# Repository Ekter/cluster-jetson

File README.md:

# cluster-jetson
cluster of jetson nano

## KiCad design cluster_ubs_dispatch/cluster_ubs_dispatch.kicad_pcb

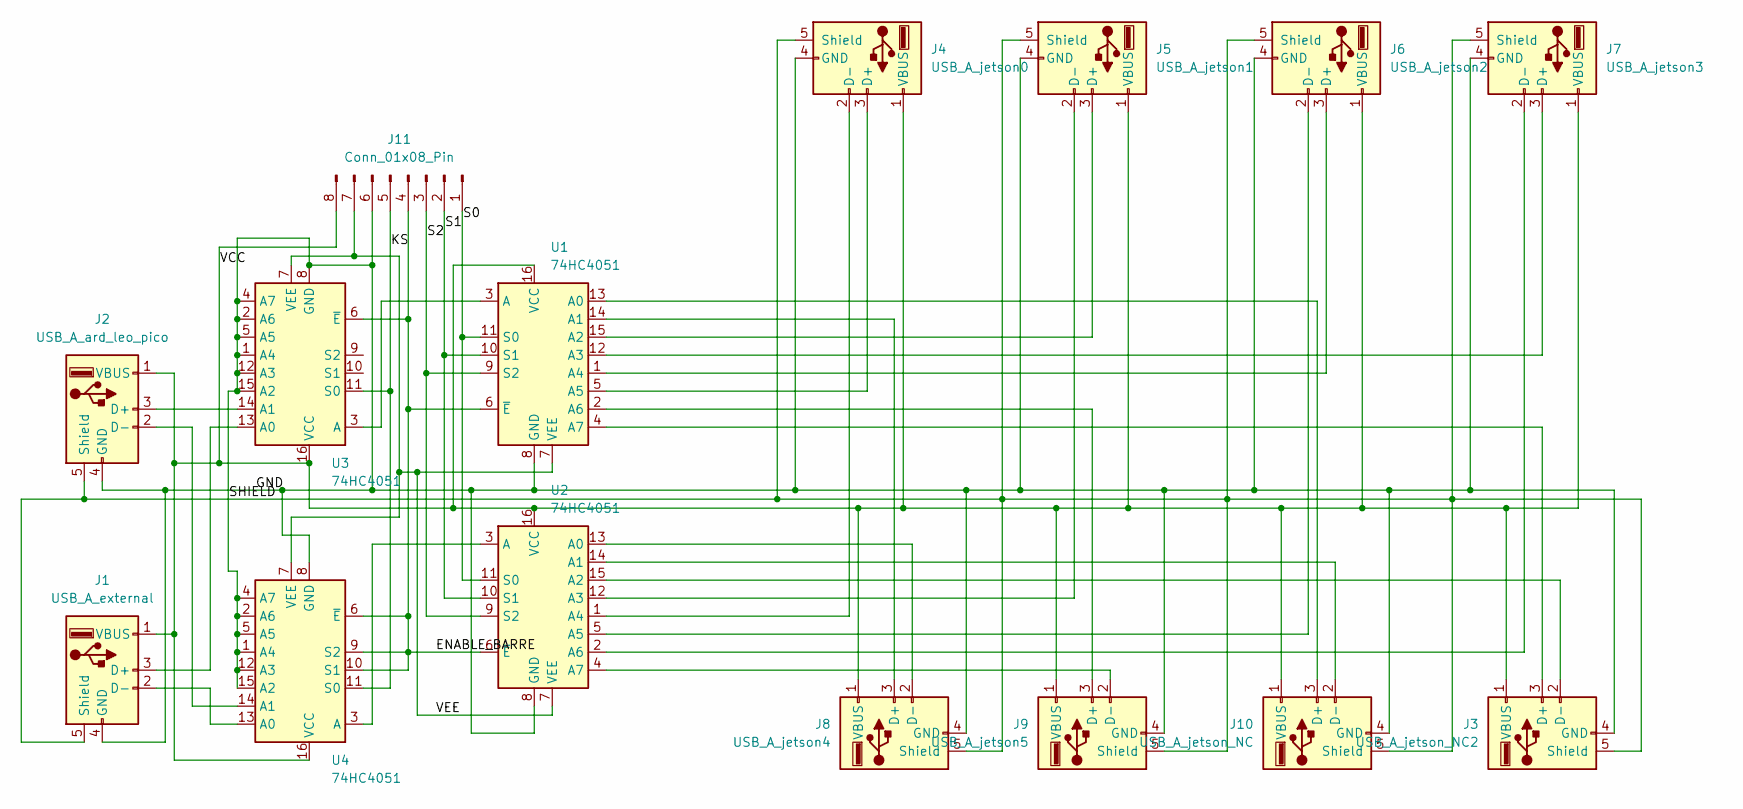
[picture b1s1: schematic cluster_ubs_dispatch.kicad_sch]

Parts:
J1: USB_A_external; USB_A_TE_292303-7_Horizontal
J2: USB_A_ard_leo_pico; USB_A_TE_292303-7_Horizontal
J3: USB_A_jetson_NC2; USB_A_TE_292303-7_Horizontal
J4: USB_A_jetson0; USB_A_TE_292303-7_Horizontal
J5: USB_A_jetson1; USB_A_TE_292303-7_Horizontal
J6: USB_A_jetson2; USB_A_TE_292303-7_Horizontal
J7: USB_A_jetson3; USB_A_TE_292303-7_Horizontal
J8: USB_A_jetson4; USB_A_TE_292303-7_Horizontal
J9: USB_A_jetson5; USB_A_TE_292303-7_Horizontal
J10: USB_A_jetson_NC; USB_A_TE_292303-7_Horizontal
J11: Conn_01x08_Pin; PinHeader_1x08_P2.54mm_Vertical
U1, U2, U3, U4: 74HC4051; SOIC-16_3.9x9.9mm_P1.27mm

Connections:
/ENABLE_BARRE: J11.4, U1.6 (~E), U2.6 (~E), U3.6 (~E), U3.9 (S2), U3.10 (S1), U4.6 (~E), U4.9 (S2), U4.10 (S1)
/KS: J11.5, U3.11 (S0), U4.11 (S0)
/S0: J11.1, U1.11 (S0), U2.11 (S0)
/S1: J11.2, U1.10 (S1), U2.10 (S1)
/S2: J11.3, U1.9 (S2), U2.9 (S2)
/VCC: J1.1 (VBUS), J2.1 (VBUS), J3.1 (VBUS), J4.1 (VBUS), J5.1 (VBUS), J6.1 (VBUS), J7.1 (VBUS), J8.1 (VBUS), J9.1 (VBUS), J10.1 (VBUS), J11.8, U1.16 (VCC), U2.16 (VCC), U3.16 (VCC), U4.16 (VCC)
/VEE: J11.7, U1.7 (VEE), U2.7 (VEE), U3.7 (VEE), U4.7 (VEE)
unnamed: J1.3 (D+), U3.13 (A0)
unnamed: J1.2 (D-), U4.13 (A0)
unnamed: J2.3 (D+), U3.14 (A1)
unnamed: J2.2 (D-), U4.14 (A1)
unnamed: J3.3 (D+), U1.4 (A7)
unnamed: J3.2 (D-), U2.15 (A2)
unnamed: J4.3 (D+), U1.5 (A5)
unnamed: J4.2 (D-), U2.1 (A4)
unnamed: J5.3 (D+), U1.15 (A2)
unnamed: J5.2 (D-), U2.12 (A3)
unnamed: J6.3 (D+), U1.1 (A4)
unnamed: J6.2 (D-), U2.5 (A5)
unnamed: J7.3 (D+), U1.12 (A3)
unnamed: J7.2 (D-), U2.2 (A6)
unnamed: J8.3 (D+), U1.14 (A1)
unnamed: J8.2 (D-), U2.13 (A0)
unnamed: J9.3 (D+), U1.2 (A6)
unnamed: J9.2 (D-), U2.4 (A7)
unnamed: J10.3 (D+), U1.13 (A0)
unnamed: J10.2 (D-), U2.14 (A1)
unnamed: U1.3 (A), U3.3 (A)
unnamed: U2.3 (A), U4.3 (A)

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
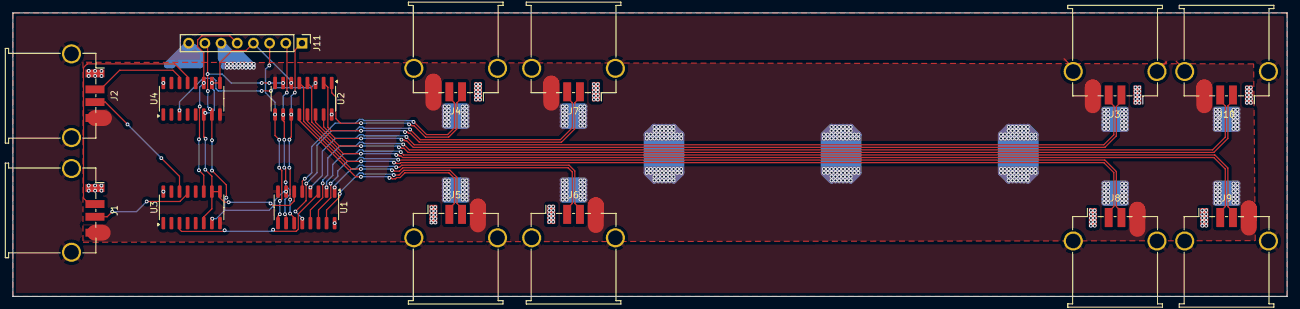
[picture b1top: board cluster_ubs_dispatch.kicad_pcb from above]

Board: 2 copper layers, 200.0 x 44.5 mm, 15 parts (0 on the bottom side), 31 nets.

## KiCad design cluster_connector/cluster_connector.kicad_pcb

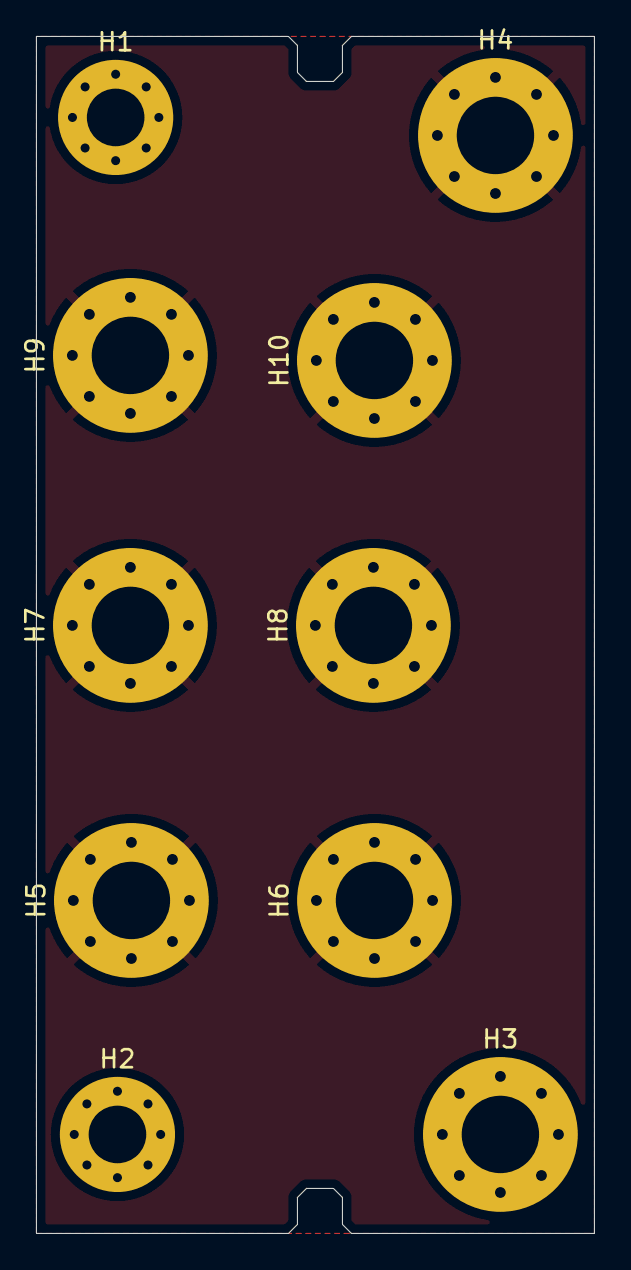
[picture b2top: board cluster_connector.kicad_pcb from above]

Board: 2 copper layers, 31.0 x 66.5 mm, 10 parts (0 on the bottom side), 2 nets, no tracks yet.

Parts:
H1, H2: MountingHole_Pad; MountingHole_3.2mm_M3_Pad_Via
H3, H4, H5, H6, H7, H8, H9, H10: MountingHole_Pad; MountingHole_4.3mm_M4_Pad_Via

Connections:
/5V: H4.1, H5.1, H6.1, H7.1, H8.1, H9.1, H10.1
/GND: H1.1, H2.1, H3.1

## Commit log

2025-11-17 two pcbs for power and usb control of the jetson nanos
2026-01-01 missing additional S connection
2026-01-01 fix: remove lock file
